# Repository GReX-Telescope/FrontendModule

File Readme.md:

# GReX Frontend Module

You'll need:
- [Rust](https://rustup.rs/)
- ARM Rust toolchain
    - `rustup target add thumbv7em-none-eabihf`
- [just](https://github.com/casey/just)
    - `cargo install just`
- [cross](https://github.com/cross-rs/cross) (which requires either Docker or Podman)
    - `cargo install cross --git https://github.com/cross-rs/cross`
- [probe-rs](https://probe.rs/)
    - `cargo install probe-rs --features cli,ftdi`

## Hardware

For assembly, access the interactive BOM [here](https://grex-telescope.github.io/FrontendModule/hardware/bom/ibom.html)

## Software

### Building

Build for the current architecture

`just build-cli`

### For the RPi in the box

`just build-cli-pi`

The resulting binary is in `target/armv7-unknown-linux-musleabihf/release/cli` which you can copy to the Pi, `chmod +x` if you need, and run.

## Firmware

### Building

`just build-firmware`

The resulting binary (elf) is in target/thumbv6m-none-eabi/release/firmware

### Flashing

Using a JLink in CMSIS-DAP mode

`just flash-firmware`

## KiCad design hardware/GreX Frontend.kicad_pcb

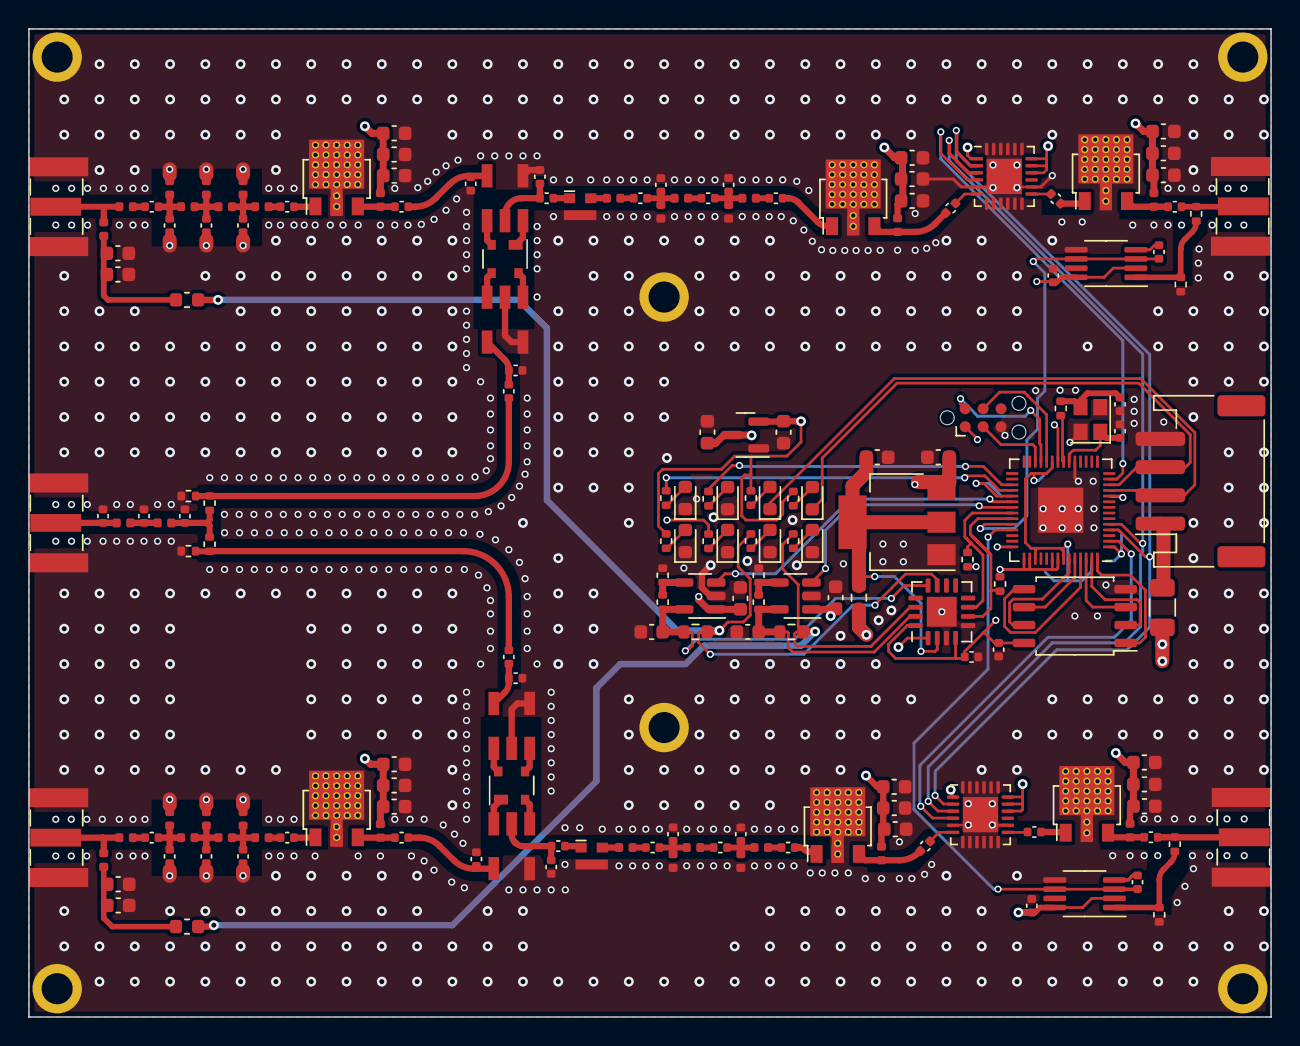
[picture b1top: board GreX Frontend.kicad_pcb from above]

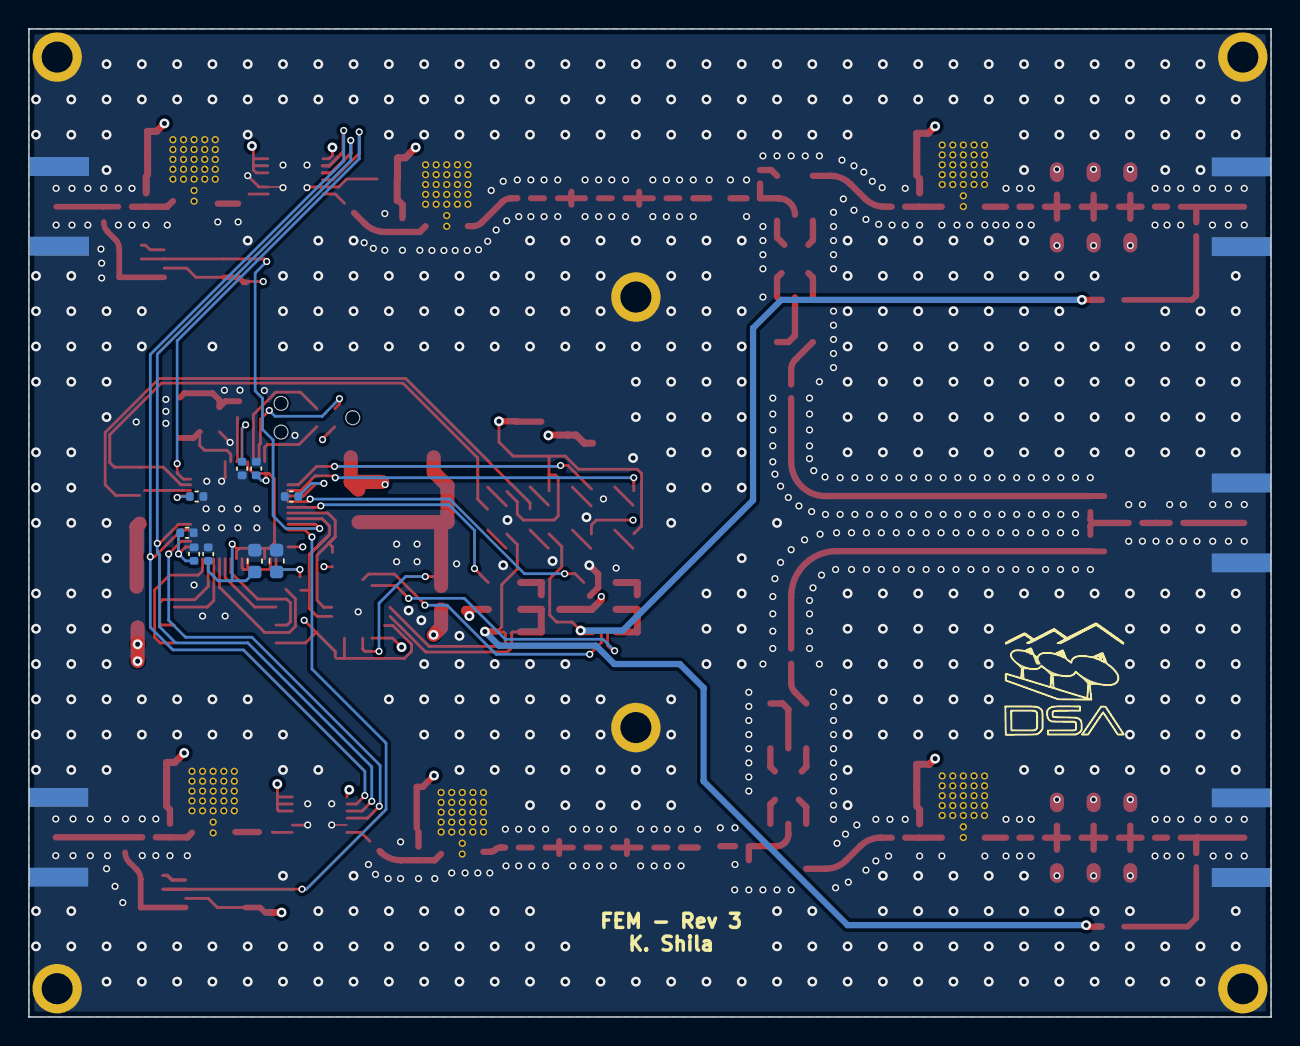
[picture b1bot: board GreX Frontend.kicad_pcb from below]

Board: 4 copper layers, 88.0 x 70.0 mm, 199 parts (10 on the bottom side), 116 nets.

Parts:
C1, C34, C38, C52, C55, C59, C75, C79: 1.2n; C_0603_1608Metric
C2, C35, C39, C53, C56, C60, C76, C80: 68p; C_0603_1608Metric
C3, C4, C5, C7, C9, C10, C17, C19, C33, C40, C54, C61, C74, C78: 1u; C_0603_1608Metric
C6, C8: 22u; C_0603_1608Metric
C11, C13, C15, C16, C18, C20, C21, C22, C23, C29, C30, C31, C32, C36, C37, C41, C57, C58, C62, C77, C81, C82, C87: 100n; C_0402_1005Metric
C12, C14: 15p; C_0402_1005Metric
C24, C28, C42, C46: 8.2p; C_0402_1005Metric
C25, C27, C43, C45: 16p; C_0402_1005Metric
C26, C44: 3.9p; C_0402_1005Metric
C47, C51, C69, C73: 1.3p; C_0402_1005Metric
C48, C50, C70, C72: 5p; C_0402_1005Metric
C49, C71: 1.6; C_0402_1005Metric
C63, C65: 1.8p; C_0402_1005Metric
C64: 4p; C_0402_1005Metric
C66, C67, C68, C83, C84, C85, C86, C88: DNP; C_0402_1005Metric
D1, D2, D3, D4: RED; LED_0603_1608Metric
D5, D6: GREEN; LED_0603_1608Metric
D7, D8: BLUE; LED_0603_1608Metric
F1: Polyfuse; Fuse_1206_3216Metric
H1, H2, H3, H4, H5, H6: MountingHole_2.2mm_M2_ISO7380_Pad
J1, J4, J5, J6, J7: Conn_Coaxial; SMA_Samtec_SMA-J-P-X-ST-EM1_EdgeMount
J2: Screw_Terminal_01x04; JST_PH_S4B-PH-SM4-TB_1x04-1MP_P2.00mm_Horizontal
J3: PROG; Tag-Connect_TC2030-IDC-NL_2x03_P1.27mm_Vertical
L1, L22: 47u; L_0603_1608Metric
L2, L23, L35, L36: 43n; L_0402_1005Metric
L3, L7, L10, L14: 24n; L_0402_1005Metric
L4, L6, L11, L13: 12n; L_0402_1005Metric
L5, L12: 51n; L_0402_1005Metric
L8, L9, L24, L25: 1000n; L_0402_1005Metric
L15, L21, L28, L34: 8.7n; L_0402_1005Metric
L16, L20, L29, L33: 2.2n; L_0402_1005Metric
L17, L19, L30, L32: 13n; L_0402_1005Metric
L18, L31: 27n; L_0402_1005Metric
L26, L27: 9.1n; L_0402_1005Metric
R1, R3: 82k; R_0402_1005Metric
R2, R4: 24k; R_0402_1005Metric
R5: 0.2; R_0603_1608Metric
R6, R7: 1; R_0603_1608Metric
R8, R9, R10, R11, R12, R13, R14, R15, R16: 1k; R_0402_1005Metric
R17, R18: 4.7k; R_0402_1005Metric
R19, R22: 100; R_0402_1005Metric
R20, R21: 68; R_0402_1005Metric
R23, R25: 226; R_0402_1005Metric
R24, R26: 28; R_0402_1005Metric
U1: DSA_Logo; DSAlogo_letterswhite
U2: XC6206PxxxMR; SOT-23
U3: AMS1117-5.0; SOT-223-3_TabPin2
U4, U5: SPX3819M5-L; SOT-23-5
U6: INA3221; Texas_RGV_S-PVQFN-N16_EP2.1x2.1mm
U7: IS25LP080D-JBLE; SOIC-8_5.275x5.275mm_P1.27mm
U8: RP2040; QFN-56-1EP_7x7mm_P0.4mm_EP3.2x3.2mm
U9, U10: PAT1220-C-3DB; RF_Attenuator_Susumu_PAT1220
U11, U13, U14, U16, U20, U21: ADL5611; SOT89-HighTemp
U12, U15: HMC1122; LFCSP-24-1EP_4x4mm_P0.5mm_EP2.5x2.5mm
U17, U19, U23, U25: TC4-19G2; AT224
U18, U24: BAT-15-099R; SOT-143
U22, U26: AD8314; MSOP-8_3x3mm_P0.65mm
Y1: 2TJ412000NYGBC; Crystal_SMD_2520-4Pin_2.5x2.0mm

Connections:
+1V1: C15.1, C16.1, C17.2, U8.23 (DVDD), U8.45 (VREG_VOUT), U8.50 (DVDD)
+3V3: C7.2, C11.1, C13.1, C18.1, C19.2, C20.1, C21.1, C22.1, C23.1, J3.1, R8.1, R14.1, R15.1, R17.1, R18.1, U2.2 (VO), U6.4 (VS), U6.16 (VPU), U7.8 (VCC), U8.1 (IOVDD), U8.10 (IOVDD), U8.22 (IOVDD), U8.33 (IOVDD), U8.42 (IOVDD), U8.43 (ADC_AVDD), U8.44 (VREG_IN), U8.48 (USB_VDD), U8.49 (IOVDD)
+5VA: C33.2, C34.2, C35.2, C38.2, C39.2, C40.2, C54.2, C55.2, C56.2, C59.2, C60.2, C61.2, C74.2, C75.2, C76.2, C78.2, C79.2, C80.2, C82.2, C87.2, L8.1, L9.1, L24.1, L25.1, L35.1, L36.1, R5.2, R9.1, U6.1 (IN-3), U12.1 (P/S), U12.16 (PUP2), U12.17 (PUP1), U12.18 (VDD), U15.1 (P/S), U15.16 (PUP2), U15.17 (PUP1), U15.18 (VDD), U22.2 (ENBL), U22.8 (VPOS), U26.2 (ENBL), U26.8 (VPOS)
/RF/IF Filter 1 /In: L3.1, U9.2
/RF/IF Filter 1 /Out: C28.2, U11.1
/RF/IF Filter 2/In: L10.1, U10.2
/RF/IF Filter 2/Out: C46.2, U14.1
/RF/Input Stage 1/ADL5611/In: C51.1, U20.1
/RF/Input Stage 1/Input Filter/In: J1.1 (In), L2.2, L15.1
/RF/Input Stage 1/OUT: C77.1, C84.1, U23.4
/RF/Input Stage 2/ADL5611/In: C73.1, U21.1
/RF/Input Stage 2/Input Filter/In: J6.1 (In), L23.2, L28.1
/RF/Input Stage 2/OUT: C66.1, C81.1, U17.6 (PD)
/RF/LO Filter/In: C63.1, J4.1 (In), L26.1
/RF/LO Filter/Out: C65.1, L27.2, R20.1, R21.2
/RF/Mixer/IF: C32.1, C67.1, U17.2 (SCT)
/RF/Mixer/LO: C29.2, C68.1, U19.4
/RF/Mixer_1/IF: C31.1, C85.1, U23.2 (SCT)
/RF/Mixer_1/LO: C30.2, C86.1, U25.6 (PD)
/RF/Output Stage 1/Power Sensor/RF_In: C41.2, J5.1 (In), R23.1
/RF/Output Stage 2/Power Sensor/RF_In: C62.2, J7.1 (In), R25.1
ATTEN_LE_1: U8.13 (GPIO10), U12.4 (LE)
ATTEN_LE_2: U8.2 (GPIO0), U15.4 (LE)
CLK: U8.4 (GPIO2), U12.2 (CLK), U15.2 (CLK)
GND: C1.1, C2.1, C3.1, C4.1, C5.1, C6.1, C7.1, C8.1, C9.1, C10.1, C11.2, C12.2, C13.2, C14.2, C15.2, C16.2, C17.1, C18.2, C19.1, C20.2, C21.2, C22.2, C23.2, C25.2, C27.2, C33.1, C34.1, C35.1, C38.1, C39.1, C40.1, C43.2, C45.2, C48.1, C49.1, C50.1, C52.1, C53.1, C54.1, C55.1, C56.1, C59.1, C60.1, C61.1, C63.2, C64.2, C65.2, C66.2, C67.2, C68.2, C70.1, C71.1, C72.1, C74.1, C75.1, C76.1, C78.1, C79.1, C80.1, C82.1, C84.2, C85.2, C86.2, C87.1, D1.1 (K), D2.1 (K), D3.1 (K), D4.1 (K), D5.1 (K), D6.1 (K), H1.1, H2.1, H3.1, H4.1, H5.1, H6.1, J1.2 (Ext), J2.4, J3.5, J4.2 (Ext), J5.2 (Ext), J6.2 (Ext), J7.2 (Ext), L4.1, L6.1, L11.1, L13.1, L16.2, L18.2, L20.2, L29.2, L31.2, L33.2, R2.2, R4.2, R19.2, R22.1, R24.1, R26.1, U2.1 (GND), U3.1 (GND), U4.2 (GND), U5.2 (GND), U6.3 (GND), U6.5 (A0), U6.17 (EP), U7.4 (GND), U8.19 (TESTEN), U8.57 (GND), U9.3, U10.3, U11.2 (GND), U12.5 (GND), U12.7 (GND), U12.8 (GND), U12.9 (GND), U12.10 (GND), U12.11 (GND), U12.12 (GND), U12.14 (GND), U12.19 (D5), U12.20 (D4), U12.21 (D3), U12.22 (D2), U12.23 (D1), U12.24 (D0), U12.25 (GND), U13.2 (GND), U14.2 (GND), U15.5 (GND), U15.7 (GND), U15.8 (GND), U15.9 (GND), U15.10 (GND), U15.11 (GND), U15.12 (GND), U15.14 (GND), U15.19 (D5), U15.20 (D4), U15.21 (D3), U15.22 (D2), U15.23 (D1), U15.24 (D0), U15.25 (GND), U16.2 (GND), U17.4, U19.2 (SCT), U19.6 (PD), U20.2 (GND), U21.2 (GND), U22.5 (GND), U23.6 (PD), U25.2 (SCT), U25.4, U26.5 (GND), Y1.2, Y1.4
MOSI: U8.5 (GPIO3), U12.3 (SERIN), U15.3 (SERIN)
unnamed: C1.2, C2.2, L1.2, L2.1
unnamed: C14.1, R16.1, Y1.3
unnamed: C24.1, L3.2
unnamed: C24.2, C25.1, L4.2, L5.1
unnamed: C26.1, L5.2
unnamed: C26.2, C27.1, L6.2, L7.1
unnamed: C28.1, L7.2
unnamed: C29.1, R21.1, R22.2
unnamed: C30.1, R19.1, R20.2
unnamed: C31.2, U9.1
unnamed: C32.2, U10.1
unnamed: C36.1, L8.2, U11.3
unnamed: C37.2, U13.1
unnamed: C41.1, L9.2, U13.3
unnamed: C42.1, L10.2
unnamed: C42.2, C43.1, L11.2, L12.1
unnamed: C44.1, L12.2
unnamed: C44.2, C45.1, L13.2, L14.1
unnamed: C46.1, L14.2
unnamed: C47.1, C48.2, L16.1, L17.1
unnamed: C47.2, L15.2
unnamed: C49.2, L17.2, L18.1, L19.1
unnamed: C50.2, L19.2, L20.1, L21.1
unnamed: C51.2, L21.2
unnamed: C52.2, C53.2, L22.2, L23.1
unnamed: C57.1, L24.2, U14.3
unnamed: C58.2, U16.1
unnamed: C62.1, L25.2, U16.3
unnamed: C64.1, L26.2, L27.1
unnamed: C69.1, C70.2, L29.1, L30.1
unnamed: C69.2, L28.2
unnamed: C71.2, L30.2, L31.1, L32.1
unnamed: C72.2, L32.2, L33.1, L34.1
unnamed: C73.2, L34.2
unnamed: C77.2, L35.2, U20.3
unnamed: C81.2, L36.2, U21.3
unnamed: D1.2 (A), R8.2
unnamed: D2.2 (A), R9.2
unnamed: D3.2 (A), R10.2
unnamed: D4.2 (A), R11.2
unnamed: D5.2 (A), R12.2
unnamed: D6.2 (A), R13.2
unnamed: D7.2 (A), R14.2
unnamed: D8.2 (A), R15.2
unnamed: F1.1, J2.1
unnamed: C3.2, C4.2, C5.2, C6.2, F1.2, U2.3 (VI), U3.3 (VI), U4.1 (IN), U5.1 (IN)
unnamed: R1.2, R2.1, U4.4 (ADJ)
unnamed: R3.2, R4.1, U5.4 (ADJ)
unnamed: U7.1 (CE#), U8.56 (QSPI_SS)
unnamed: U7.6 (SCK), U8.52 (QSPI_SCLK)
unnamed: U7.5 (SI_(IO0)), U8.53 (QSPI_SD0)
unnamed: U7.2 (SO_(IO1)), U8.55 (QSPI_SD1)
unnamed: U7.7 (nHOLD_(IO3)), U8.51 (QSPI_SD3)
unnamed: U7.3 (nWP_(IO2)), U8.54 (QSPI_SD2)
unnamed: C12.1, U8.20 (XIN), Y1.1
unnamed: R16.2, U8.21 (XOUT)
unnamed: C37.1, U12.13 (RF_A)
unnamed: C36.2, U12.6 (RF_B)
unnamed: C58.1, U15.13 (RF_A)
unnamed: C57.2, U15.6 (RF_B)
unnamed: U17.1 (S), U18.1
unnamed: U17.3 (SD), U18.2
unnamed: U18.3, U19.1 (S)
unnamed: U18.4, U19.3 (SD)
unnamed: C83.1, U22.4 (FLTR)
unnamed: R23.2, R24.2, U22.1 (RFIN)
unnamed: U23.1 (S), U24.1
unnamed: U23.3 (SD), U24.2
unnamed: U24.3, U25.1 (S)
unnamed: U24.4, U25.3 (SD)
unnamed: C88.1, U26.4 (FLTR)
unnamed: R25.2, R26.2, U26.1 (RFIN)
RF1_IF_POW: C83.2, U8.38 (GPIO26_ADC0), U22.3 (VSSET), U22.6 (V_UP)
RF1_LNA_EN: U4.3 (EN), U8.34 (GPIO22)
RF1_STATUS_LED: R12.1, U8.32 (GPIO21)
RF2_IF_POW: C88.2, U8.39 (GPIO27_ADC1), U26.3 (VSSET), U26.6 (V_UP)
RF2_LNA_EN: U5.3 (EN), U8.35 (GPIO23)
RF2_STATUS_LED: R13.1, U8.31 (GPIO20)
RXD: D8.1 (K), J2.3, U8.12 (GPIO9)
SCL: R18.2, U6.6 (SCL), U8.37 (GPIO25)
SDA: R17.2, U6.7 (SDA), U8.36 (GPIO24)
SWCLK: J3.4, U8.24 (SWCLK)
SWDIO: J3.2, U8.25 (SWD)
TXD: D7.1 (K), J2.2, U8.11 (GPIO8)
VA_+: C8.2, R5.1, U3.2 (VO), U6.2 (IN+3)
VLNA1_+: C9.2, R1.1, R6.1, U4.5 (OUT), U6.12 (IN+1)
VLNA1_-: L1.1, R6.2, R10.1, U6.11 (IN-1)
VLNA2_+: C10.2, R3.1, R7.1, U5.5 (OUT), U6.15 (IN+2)
VLNA2_-: L22.1, R7.2, R11.1, U6.14 (IN-2)
nRESET: J3.3, U8.26 (RUN)

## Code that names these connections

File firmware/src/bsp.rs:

use embedded_hal::adc::{Channel, OneShot};
use hal::{pac::UART1, Adc};
use rp2040_hal as hal;

// Crystal freq
pub const XOSC_CRYSTAL_FREQ: u32 = 12_000_000;

/// Reference voltage for ADC conversions
pub const ADC_REF_VOLT: f32 = 3.3;

// Don't forget the second stage bootloader
#[link_section = ".boot2"]
#[no_mangle]
#[used]
pub static BOOT2_FIRMWARE: [u8; 256] = rp2040_boot2::BOOT_LOADER_IS25LP080;

// And add all of our pins!
hal::bsp_pins!(
    Gpio20 { name: rf1_stat_led },
    Gpio21 { name: rf2_stat_led },
    Gpio22 { name: rf1_lna_en },
    Gpio23 { name: rf2_lna_en },
    Gpio26 { name: rf1_if_pow },
    Gpio27 { name: rf2_if_pow },
    Gpio8 {
        name: txd,
        aliases: { FunctionUart, PullDown: Txd }
    },
    Gpio9 {
        name: rxd,
        aliases: { FunctionUart, PullDown: Rxd }
    },
    Gpio24 {
        name: sda,
        aliases: { FunctionI2C, PullUp: Sda}
    },
    Gpio25 {
        name: scl,
        aliases: { FunctionI2C, PullUp: Scl}
    },
    Gpio2 {
        name: clk,
        aliases: { FunctionSpi, PullNone: Clk}
    },
    Gpio3 {
        name: sdo,
        aliases: { FunctionSpi, PullNone: Sdo}
    },
    Gpio0 { name: atten2_le },
    Gpio10 { name: atten1_le },
);

// Some type aliases
pub type UartPins = (Txd, Rxd);
pub type Uart = hal::uart::UartPeripheral<hal::uart::Enabled, UART1, UartPins>;

/// Get the 0..1 scaled floating point number representing the 12 bit ADC value
pub fn read_adc<PIN>(adc: &mut Adc, pin: &mut PIN) -> Result<f32, ()>
where
    PIN: Channel<Adc, ID = u8>,
{
    // Read the counts
    let counts: u16 = adc.read(pin).map_err(|_| ())?;
    // Scale raw 12-bit format to 0 .. 1
    let scaled = f32::from(counts) / f32::from(1u16 << 12);
    Ok(scaled.clamp(0.0, 1.0))
}

/// Read the internal temperature sensor in degrees C
pub fn read_temp<PIN>(adc: &mut Adc, pin: &mut PIN) -> Result<f32, ()>
where
    PIN: Channel<Adc, ID = u8>,
{
    // Get the raw voltage
    let v = read_adc(adc, pin)? * ADC_REF_VOLT;
    // RP2040 Datasheet 4.9.5
    Ok(27.0 - (v - 0.706) / 0.001721)
}

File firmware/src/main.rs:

#![no_std]
#![no_main]

mod atten;
mod bsp;
mod log_det;
mod mnc;

use bsp::*;
use defmt::*;
use defmt_rtt as _;
use fugit::RateExtU32;
use panic_probe as _;
use postcard::{
    accumulator::{CobsAccumulator, FeedResult},
    to_slice_cobs,
};

// Embedded Hal traits
use embedded_hal::digital::v2::OutputPin;

use hal::{
    adc::{Adc, AdcPin},
    clocks::{init_clocks_and_plls, Clock},
    entry, pac,
    sio::Sio,
    uart::{DataBits, StopBits, UartConfig, UartPeripheral},
    watchdog::Watchdog,
    I2C,
};
use rp2040_hal as hal;

#[entry]
fn main() -> ! {
    info!("FEM Booting!");
    // Setup peripherals, core clocks, etc.
    let mut pac = pac::Peripherals::take().unwrap();
    let _core = pac::CorePeripherals::take().unwrap();
    let mut watchdog = Watchdog::new(pac.WATCHDOG);
    let sio = Sio::new(pac.SIO);

    let clocks = init_clocks_and_plls(
        bsp::XOSC_CRYSTAL_FREQ,
        pac.XOSC,
        pac.CLOCKS,
        pac.PLL_SYS,
        pac.PLL_USB,
        &mut pac.RESETS,
        &mut watchdog,
    )
    .ok()
    .unwrap();

    // Setup the pins
    let pins = bsp::Pins::new(
        pac.IO_BANK0,
        pac.PADS_BANK0,
        sio.gpio_bank0,
        &mut pac.RESETS,
    );

    info!("Setting up ADC");
    // Enable the ADC peripheral and internal temperature sensor
    let mut adc = Adc::new(pac.ADC, &mut pac.RESETS);
    let mut temp_sense = adc.take_temp_sensor().unwrap();

    // Setup RF power monitor chip
    let mut rf1_if_pow = AdcPin::new(pins.rf1_if_pow.into_floating_input());
    let mut rf2_if_pow = AdcPin::new(pins.rf2_if_pow.into_floating_input());

    // Grab the UART pins and setup the peripheral (115200 baud)
    info!("Setting up UART");
    let uart_pins: UartPins = (pins.txd.into_function(), pins.rxd.into_function());
    let uart: Uart = UartPeripheral::new(pac.UART1, uart_pins, &mut pac.RESETS)
        .enable(
            UartConfig::new(115200.Hz(), DataBits::Eight, None, StopBits::One),
            clocks.peripheral_clock.freq(),
        )
        .unwrap();
    info!("Setting up GPIO");
    // Set the LNA outputs to ON by default
    let mut lna_1 = pins.rf1_lna_en.into_push_pull_output();
    let mut lna_2 = pins.rf2_lna_en.into_push_pull_output();
    lna_1.set_high().unwrap();
    lna_2.set_high().unwrap();

    // Set the RF status LEDs to off
    let mut rf1_status_led = pins.rf1_stat_led.into_push_pull_output();
    let mut rf2_status_led = pins.rf2_stat_led.into_push_pull_output();
    rf1_status_led.set_low().unwrap();
    rf2_status_led.set_low().unwrap();

    // Setup the SPI pins and initial state of the latch enable pins (high)
    // pins are implicitly used by the SPI driver
    info!("Setting up SPI");
    let mut atten1_le = pins.atten1_le.into_push_pull_output();
    atten1_le.set_low().unwrap();
    let mut atten2_le = pins.atten2_le.into_push_pull_output();
    atten2_le.set_low().unwrap();

    let spi = hal::Spi::<_, _, _, 6>::new(
        pac.SPI0,
        (pins.sdo.into_function(), pins.clk.into_function()),
    )
    .init(
        &mut pac.RESETS,
        clocks.peripheral_clock.freq(),
        1.MHz(),
        embedded_hal::spi::MODE_0,
    );

    // And setup the two attenuators
    let mut atten = atten::DualHMC624A::new(spi, atten1_le, atten2_le);
    // and set the initial state to 0
    atten.set_attenuation(0.0).unwrap();

    info!("Setting up I2C");
    // Setup I2C for the TMP100 and INA3221
    let i2c = I2C::i2c0(
        pac.I2C0,
        pins.sda.into_function(),
        pins.scl.into_function(),
        400.kHz(),
        &mut pac.RESETS,
        &clocks.system_clock,
    );

    // Setup the INA3221
    let mut ina3221 = ina3221::INA3221::new(i2c, ina3221::AddressPin::Gnd);
    match ina3221.reset() {
        Ok(_) => (),
        Err(_) => error!("INA3221 failed to reset"),
    };
    match ina3221.set_averaging(ina3221::registers::Averages::_256) {
        Ok(_) => (),
        Err(_) => error!("INA3221 failed to set averages"),
    };

    // Setup state for if good and monitor
    let mut state = mnc::State::default();

    // Setup the state for the COBS input message accumulator
    let mut in_buf = [0u8; 256];
    let mut out_buf = [0u8; 256];
    let mut cobs_buf: CobsAccumulator<256> = CobsAccumulator::new();

    info!("FEM Booted, starting main thread!");

    loop {
        // Update monitor payload in state
        mnc::update_monitor_payload(
            &mut state.last_monitor,
            &mut adc,
            &mut rf1_if_pow,
            &mut rf2_if_pow,
            &mut temp_sense,
            &mut ina3221,
        );
        // If there are bytes for us, push them to the accumulator
        if uart.uart_is_readable() {
            while let Ok(n) = uart.read_raw(&mut in_buf) {
                let buf = &in_buf[..n];
                let mut window = buf;
                'cobs: while !window.is_empty() {
                    window = match cobs_buf.feed::<transport::Command>(window) {
                        FeedResult::Consumed => break 'cobs,
                        FeedResult::OverFull(new_wind) => new_wind,
                        FeedResult::DeserError(new_wind) => new_wind,
                        FeedResult::Success {
                            data: cmd,
                            remaining,
                        } => {
                            // Handle command
                            info!("New incoming payload - {}", cmd);

                            match cmd {
                                transport::Command::Monitor => {
                                    // Serialize the last monitor payload
                                    let resp =
                                        transport::Response::Monitor(state.last_monitor.clone());
                                    info!("Sending monitor data - {}", resp);
                                    let s = to_slice_cobs(&resp, &mut out_buf).unwrap();
                                    uart.write_full_blocking(s);
                                }
                                transport::Command::Control(action) => {
                                    // Do the control thing
                                    match action {
                                        transport::Action::SetIfLevel(level) => {
                                            state.if_good_threshold = level
                                        }
                                        transport::Action::Lna1Power(en) => {
                                            if en {
                                                lna_1.set_high().unwrap();
                                            } else {
                                                lna_1.set_low().unwrap();
                                            }
                                        }
                                        transport::Action::Lna2Power(en) => {
                                            if en {
                                                lna_2.set_high().unwrap();
                                            } else {
                                                lna_2.set_low().unwrap();
                                            }
                                        }
                                        transport::Action::SetAtten(a) => {
                                            match atten.set_attenuation(a) {
                                                Ok(_) => (),
                                                Err(_) => error!("Failed to set attenuation"),
                                            }
                                        }
                                    }
                                    // Then send an ack
                                    let resp = transport::Response::Ack;
                                    let s = to_slice_cobs(&resp, &mut out_buf).unwrap();
                                    uart.write_full_blocking(s);
                                }
                            }
                            remaining
                        }
                    };
                }
            }
        }
        // Set the RF Good LEDs
        if state.last_monitor.if1_power >= state.if_good_threshold {
            rf1_status_led.set_high().unwrap();
        } else {
            rf1_status_led.set_low().unwrap();
        }
        if state.last_monitor.if2_power >= state.if_good_threshold {
            rf2_status_led.set_high().unwrap();
        } else {
            rf2_status_led.set_low().unwrap();
        }
    }
}

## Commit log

2023-01-12 First real commit
2023-01-12 First go at something reasonable
2023-01-13 voltage monitoring works
2023-01-14 calibration control
2023-01-14 clippy
2023-01-18 add pi build script
2023-01-18 blocking SPI transfer
2023-03-30 Add PCB design
2023-03-30 add link to ibom
2023-03-30 fix readme title
2023-04-12 FEM v3 Updates
2023-05-10 Remove cal circuit, swap attens, swap norflash
2023-05-26 Fix BOM errors
2023-06-08 Update FEM hardware design for production version
2023-06-08 Update cli/firmware for production FEM
2023-06-08 Build CI on nightly
2023-06-08 Actually build on nightly
2023-06-08 Just get rid of CI
2023-06-08 Use the new workspace resolver
2023-06-09 Updates for FEM v3
2023-10-27 rewrite
2023-10-27 Fix linker error, update readme
2023-10-31 Try CI builds for mnc
2023-10-31 Update CI
2023-10-31 remove musl tools from CI
2023-10-31 Explicit bin
2023-10-31 udev to linux
2023-10-31 Generate tag
2023-10-31 Add github config so we can tag
2023-10-31 add github token
2023-10-31 Only release on tag
2023-10-31 Fix typo
2023-10-31 Fix artifact typo
2023-10-31 Add firmware build
2023-10-31 Missing flip-link
2023-10-31 Another typo
2023-10-31 Add bin and hex
